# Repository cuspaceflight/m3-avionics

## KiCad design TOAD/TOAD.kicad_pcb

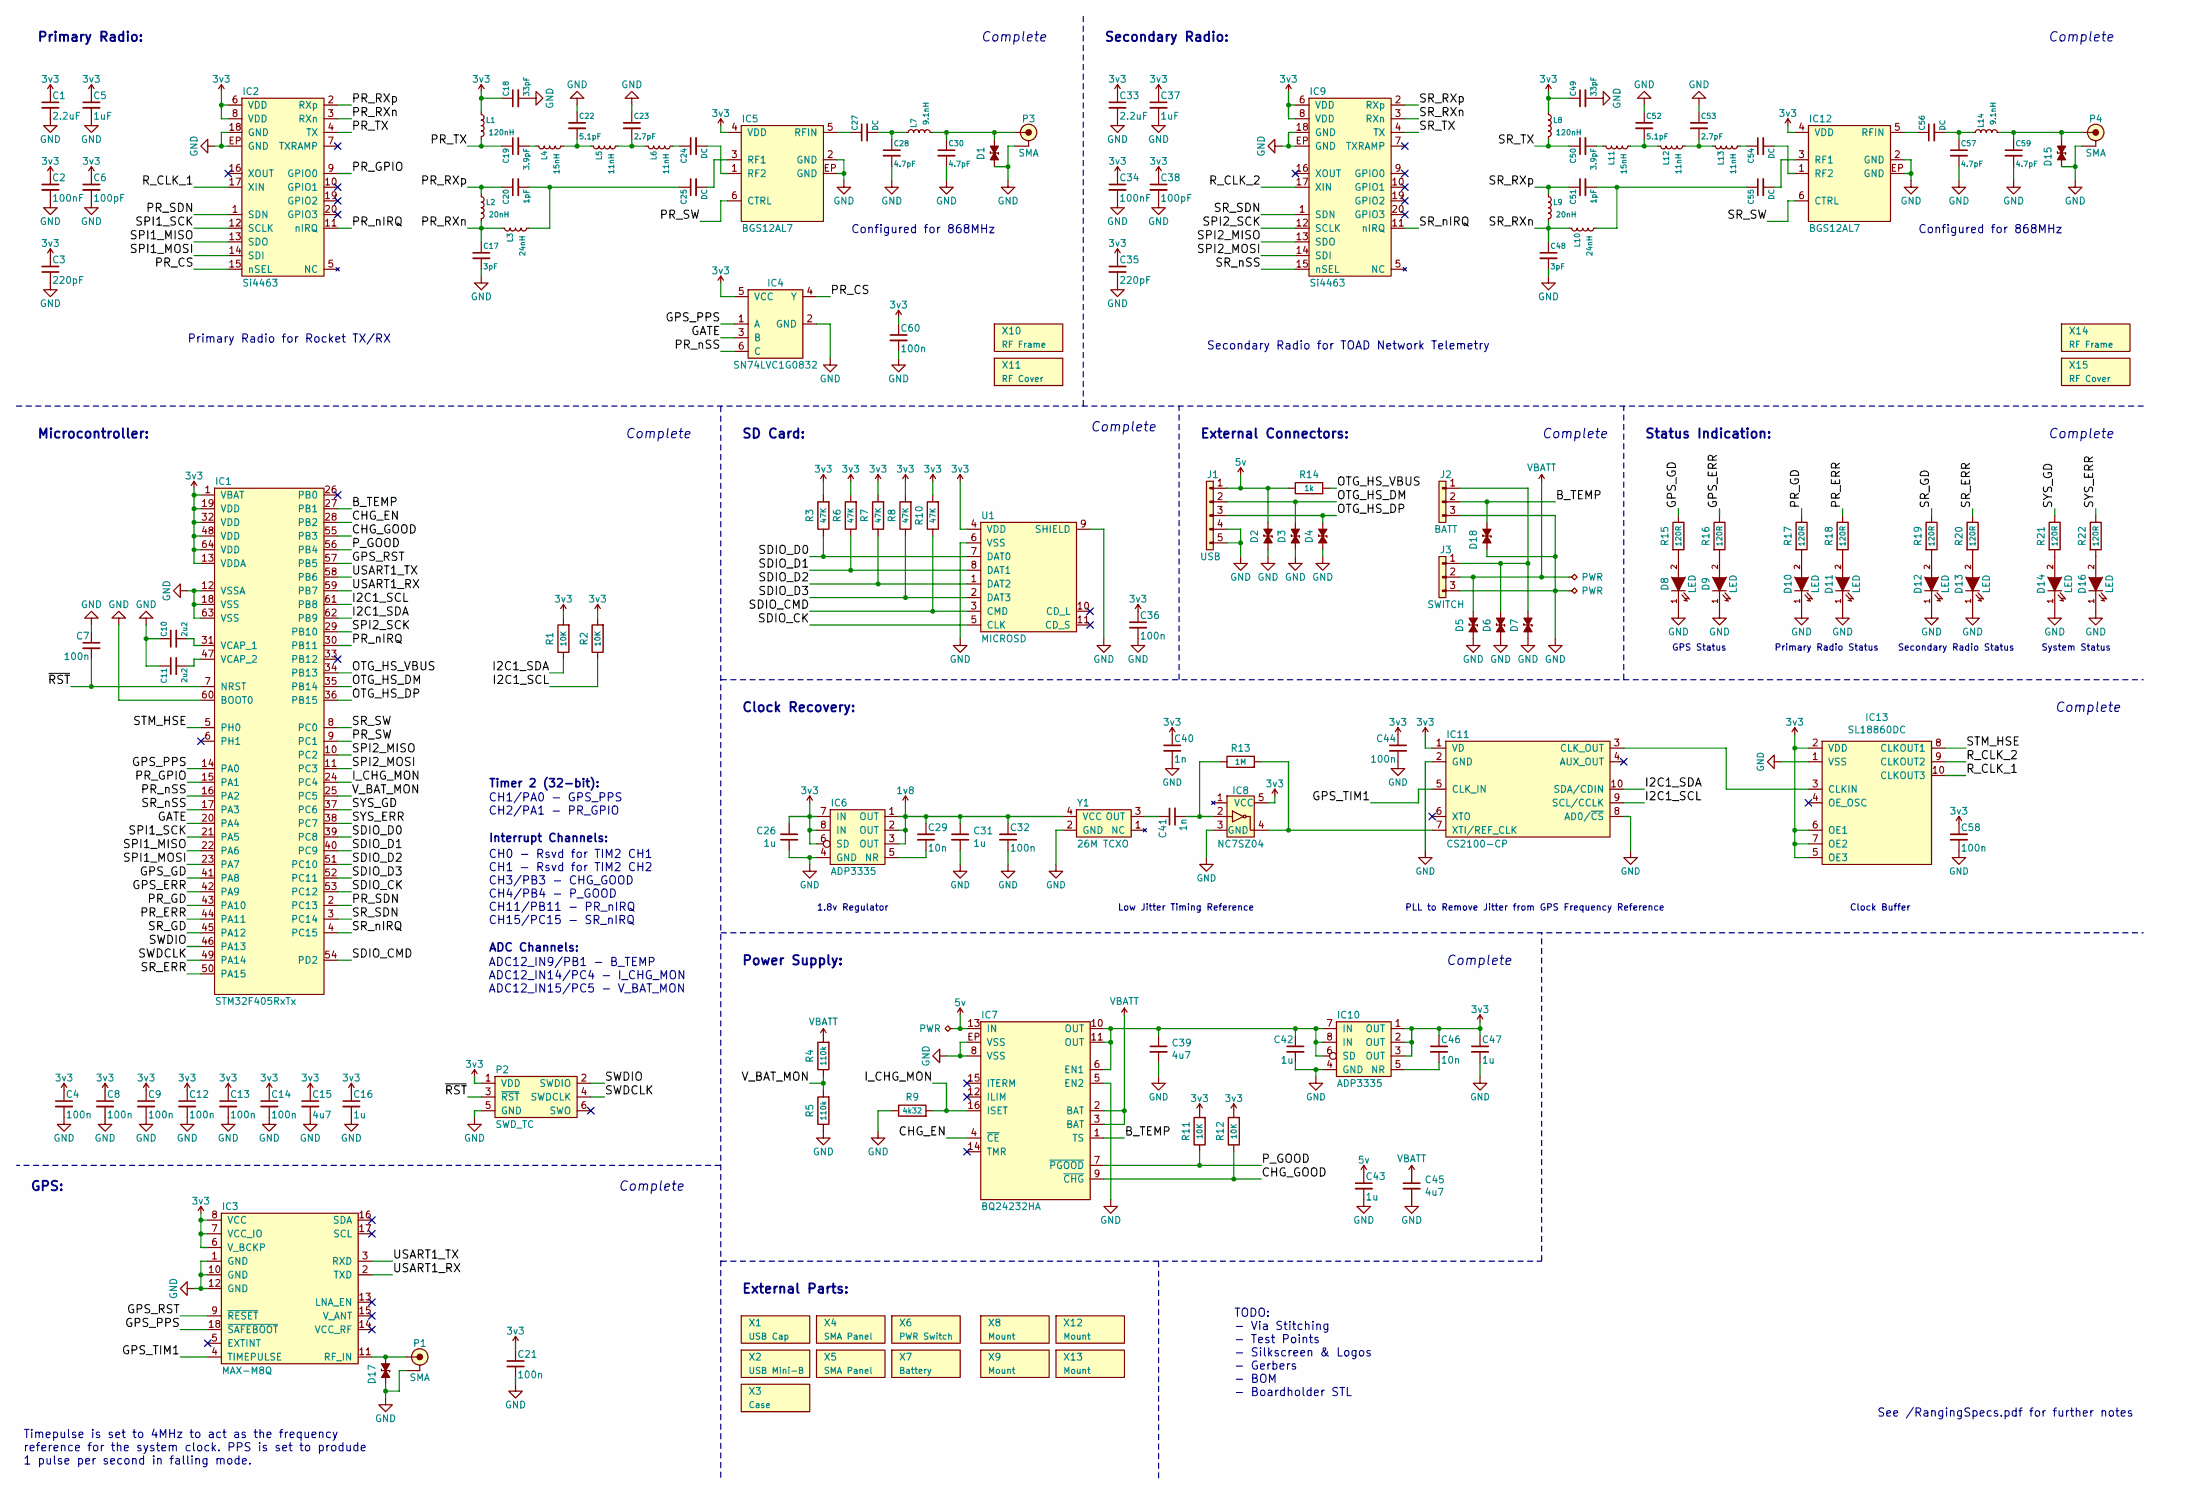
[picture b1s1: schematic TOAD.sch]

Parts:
C1, C33: 2.2uF; 0603-L; Farnell 2346896
C2, C34: 100nF; 0402; Farnell 1828860
C3, C35: 220pF; 0402; Farnell 2496800
C4, C7, C8, C9, C12, C13, C14, C60: 100n; 0402; Farnell 9402047
C5, C37: 1uF; 0603-L; Farnell 2112849
C6, C38: 100pF; 0402; Farnell 2496792
C10, C11: 2u2; 0603-L; Farnell 1797012
C15: 4u7; 0603; Farnell 2496930
C16, C26, C31, C42, C43, C47: 1u; 0603-L; Farnell 1865556
C17, C48: 3pF; 0402; Farnell 2524984
C18, C49: 33pF; 0402; Farnell 2434643
C19, C50: 3.9pF; 0402; Farnell 2672775
C20, C51: 1pF; 0402; Farnell 2133992
C21, C32, C36, C44, C58: 100n; 0603-L; Farnell 2496834
C22, C52: 5.1pF; 0402; Farnell 2688498
C23, C53: 2.7pF; 0402; Farnell 2672771
C24, C25, C27, C54, C55, C56: DC; 0402
C28, C30, C57, C59: 4.7pF; 0402; Farnell 2332509
C29, C46: 10n; 0603-L; Farnell 2496825
C39, C45: 4u7; 0603-L; Farnell 2496930
C40, C41: 1n; 0603-L; Farnell 2496882
D1, D2, D3, D4, D5, D6, D7, D15, D17, D18: ESD_DIODE; 0402-L; Farnell 2368169
D8, D10, D12, D14: LED; 0603-LED; Farnell 2290328
D9, D11, D13, D16: LED; 0603-LED; Farnell 2290329
IC1: STM32F405RxTx; LQFP-64; Farnell 2064363
IC2, IC9: Si4463; QFN-20-EP-SI; Farnell 2462637
IC3: MAX-M8Q
IC4: SN74LVC1G0832; SC-70-6; Farnell 2406965
IC5, IC12: BGS12AL7; TSLP7-4; Farnell 2480594
IC6: ADP3335; MSOP-8; Farnell 2376932
IC7: BQ24232HA; QFN-16-EP-TI; Farnell 2576286
IC8: NC7SZ04; SOT-23-5; Farnell 1417667
IC10: ADP3335; MSOP-8; Farnell 2067775
IC11: CS2100-CP; MSOP-10; Mouser 777-CS2100CP-CZZ
IC13: SL18860DC; DFN-10-SL18860DC; Mouser 634-SL18860DC
J1: USB; SIL-254P-05
J2: BATT; S03B-PASK-2; Farnell 1830748
J3: SWITCH; S03B-PASK-2; Farnell 1830748
L1, L8: 120nH; 0402; Farnell 2285871
L2, L9: 20nH; 0402; Farnell 1748728
L3, L10: 24nH; 0402; Farnell 2470344
L4, L11: 15nH; 0402; Farnell 1762621
L5, L6, L12, L13: 11nH; 0402; Farnell 2116067
L7, L14: 9.1nH; 0402; Farnell 1762616
P1: SMA; SMA-EDGE
P2: SWD_TC; TC2030-NL
P3, P4: SMA; SMA-EDGE; Farnell 1608592
R1, R2, R11, R12: 10K; 0603-L; Farnell 9238603
R3, R6, R7, R8, R10: 47K; 0603-L; Farnell 9238689
R4, R5: 110k; 0603-L; Farnell 2502402
R9: 4k32; 0603-L; Farnell 2670808
R13: 1M; 0603-L; Farnell 1469746
R14: 1k; 0603-L; Farnell 2309108
R15, R16, R17, R18, R19, R20, R21, R22: 120R; 0603-L; Farnell 9238379
U1: MICROSD; MICROSD_MOLEX_503398-1892; Farnell 2358234
X1: USB Cap
X2: USB Mini-B
X3: Case
X4, X5: SMA Panel; Farnell 2096227
X6: PWR Switch
X7: Battery; Farnell 2401856
X8, X9, X12, X13: Mount; M3_MOUNT
X10, X14: RF Frame; BMI-S-201-F; Farnell 2497715
X11, X15: RF Cover; Farnell 2497714
Y1: 26M TCXO; XTAL-25x20; Farnell 2405785

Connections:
1v8: C29.1, C31.1, C32.1, IC6.1 (OUT), IC6.2 (OUT), IC6.3 (OUT), Y1.4 (VCC)
3v3: C1.1, C2.1, C3.1, C4.1, C5.1, C6.1, C8.1, C9.1, C12.1, C13.1, C14.1, C15.1, C16.1, C18.1, C21.1, C26.1, C33.1, C34.1, C35.1, C36.1, C37.1, C38.1, C40.1, C44.1, C46.1, C47.1, C49.1, C58.1, C60.1, IC1.1 (VBAT), IC1.13 (VDDA), IC1.19 (VDD), IC1.32 (VDD), IC1.48 (VDD), IC1.64 (VDD), IC2.6 (VDD), IC2.8 (VDD), IC3.6 (V_BCKP), IC3.7 (VCC_IO), IC3.8 (VCC), IC4.5 (VCC), IC5.4 (VDD), IC6.6 (SD), IC6.7 (IN), IC6.8 (IN), IC8.5 (VCC), IC9.6 (VDD), IC9.8 (VDD), IC10.1 (OUT), IC10.2 (OUT), IC10.3 (OUT), IC11.1 (VD), IC12.4 (VDD), IC13.2 (VDD), IC13.5 (OE3), IC13.6 (OE1), IC13.7 (OE2), L1.1, L8.1, P2.1 (VDD), R1.2, R2.2, R3.2, R6.2, R7.2, R8.2, R10.2, R11.2, R12.2, U1.4 (VDD)
5v: C43.1, D2.1, IC7.13 (IN), J1.1, R14.1
/B_TEMP: D18.1, IC1.27 (PB1), IC7.1 (TS), J2.2
/CHG_EN: IC1.28 (PB2), IC7.4 (~CE)
/CHG_GOOD: IC1.55 (PB3), IC7.9 (~CHG), R12.1
/GATE: IC1.20 (PA4), IC4.3 (B)
/GPS_ERR: IC1.42 (PA9), R16.1
/GPS_GD: IC1.41 (PA8), R15.1
/GPS_PPS: IC1.14 (PA0), IC3.18 (~SAFEBOOT), IC4.1 (A)
/GPS_RST: IC1.57 (PB5), IC3.9 (~RESET)
/GPS_TIM1: IC3.4 (TIMEPULSE), IC11.5 (CLK_IN)
/I2C1_SCL: IC1.61 (PB8), IC11.9 (SCL/CCLK), R2.1
/I2C1_SDA: IC1.62 (PB9), IC11.10 (SDA/CDIN), R1.1
/I_CHG_MON: IC1.24 (PC4), IC7.16 (ISET), R9.2
/OTG_HS_DM: D3.1, IC1.35 (PB14), J1.2
/OTG_HS_DP: D4.1, IC1.36 (PB15), J1.3
/OTG_HS_VBUS: IC1.34 (PB13), R14.2
/PR_CS: IC2.15 (nSEL), IC4.4 (Y)
/PR_ERR: IC1.44 (PA11), R18.1
/PR_GD: IC1.43 (PA10), R17.1
/PR_GPIO: IC1.15 (PA1), IC2.9 (GPIO0)
/PR_RXn: C17.1, IC2.3 (RXn), L2.2, L3.1
/PR_RXp: C20.1, IC2.2 (RXp), L2.1
/PR_SDN: IC1.2 (PC13), IC2.1 (SDN)
/PR_SW: IC1.9 (PC1), IC5.6 (CTRL)
/PR_TX: C19.1, IC2.4 (TX), L1.2
/PR_nIRQ: IC1.30 (PB11), IC2.11 (nIRQ)
/PR_nSS: IC1.16 (PA2), IC4.6 (C)
/P_GOOD: IC1.56 (PB4), IC7.7 (~PGOOD), R11.1
/R_CLK_1: IC2.17 (XIN), IC13.10 (CLKOUT3)
/R_CLK_2: IC9.17 (XIN), IC13.9 (CLKOUT2)
/SDIO_CK: IC1.53 (PC12), U1.5 (CLK)
/SDIO_CMD: IC1.54 (PD2), R10.1, U1.3 (CMD)
/SDIO_D0: IC1.39 (PC8), R3.1, U1.7 (DAT0)
/SDIO_D1: IC1.40 (PC9), R6.1, U1.8 (DAT1)
/SDIO_D2: IC1.51 (PC10), R7.1, U1.1 (DAT2)
/SDIO_D3: IC1.52 (PC11), R8.1, U1.2 (DAT3)
/SPI1_MISO: IC1.22 (PA6), IC2.13 (SDO)
/SPI1_MOSI: IC1.23 (PA7), IC2.14 (SDI)
/SPI1_SCK: IC1.21 (PA5), IC2.12 (SCLK)
/SPI2_MISO: IC1.10 (PC2), IC9.13 (SDO)
/SPI2_MOSI: IC1.11 (PC3), IC9.14 (SDI)
/SPI2_SCK: IC1.29 (PB10), IC9.12 (SCLK)
/SR_ERR: IC1.50 (PA15), R20.1
/SR_GD: IC1.45 (PA12), R19.1
/SR_RXn: C48.1, IC9.3 (RXn), L9.2, L10.1
/SR_RXp: C51.1, IC9.2 (RXp), L9.1
/SR_SDN: IC1.3 (PC14), IC9.1 (SDN)
/SR_SW: IC1.8 (PC0), IC12.6 (CTRL)
/SR_TX: C50.1, IC9.4 (TX), L8.2
/SR_nIRQ: IC1.4 (PC15), IC9.11 (nIRQ)
/SR_nSS: IC1.17 (PA3), IC9.15 (nSEL)
/STM_HSE: IC1.5 (PH0), IC13.8 (CLKOUT1)
/SWDCLK: IC1.49 (PA14), P2.4 (SWDCLK)
/SWDIO: IC1.46 (PA13), P2.2 (SWDIO)
/SYS_ERR: IC1.38 (PC7), R22.1
/SYS_GD: IC1.37 (PC6), R21.1
/USART1_RX: IC1.59 (PB7), IC3.2 (TXD)
/USART1_TX: IC1.58 (PB6), IC3.3 (RXD)
/V_BAT_MON: IC1.25 (PC5), R4.1, R5.2
/~RST: C7.2, IC1.7 (NRST), P2.3 (~RST)
GND: C1.2, C2.2, C3.2, C4.2, C5.2, C6.2, C7.1, C8.2, C9.2, C10.1, C11.1, C12.2, C13.2, C14.2, C15.2, C16.2, C17.2, C18.2, C21.2, C22.1, C23.1, C26.2, C28.2, C30.2, C31.2, C32.2, C33.2, C34.2, C35.2, C36.2, C37.2, C38.2, C39.2, C40.2, C42.2, C43.2, C44.2, C45.2, C47.2, C48.2, C49.2, C52.1, C53.1, C57.2, C58.2, C59.2, C60.2, D1.2, D2.2, D3.2, D4.2, D5.2, D6.2, D7.2, D8.1 (K), D9.1 (K), D10.1 (K), D11.1 (K), D12.1 (K), D13.1 (K), D14.1 (K), D15.2, D16.1 (K), D17.2, D18.2, IC1.12 (VSSA), IC1.18 (VSS), IC1.60 (BOOT0), IC1.63 (VSS), IC2.18 (GND), IC2.EP (GND), IC3.1 (GND), IC3.10 (GND), IC3.12 (GND), IC4.2 (GND), IC5.2 (GND), IC5.EP (GND), IC6.4 (GND), IC7.5 (EN2), IC7.8 (VSS), IC7.EP (VSS), IC8.3 (GND), IC9.18 (GND), IC9.EP (GND), IC10.4 (GND), IC11.2 (GND), IC11.8 (AD0/~CS), IC12.2 (GND), IC12.EP (GND), IC13.1 (VSS), J1.4, J1.5, J2.3, J3.3, P1.2 (GND), P2.5 (GND), P3.2 (GND), P4.2 (GND), R5.1, R9.1, U1.6 (VSS), U1.9 (SHIELD), Y1.2 (GND)
unnamed: C10.2, IC1.31 (VCAP_1)
unnamed: C11.2, IC1.47 (VCAP_2)
unnamed: C19.2, L4.1
unnamed: C20.2, C25.1, L3.2
unnamed: C22.2, L4.2, L5.1
unnamed: C23.2, L5.2, L6.1
unnamed: C24.1, L6.2
unnamed: C24.2, IC5.1 (RF2)
unnamed: C25.2, IC5.3 (RF1)
unnamed: C27.1, IC5.5 (RFIN)
unnamed: C27.2, C28.1, L7.1
unnamed: C29.2, IC6.5 (NR)
unnamed: C30.1, D1.1, L7.2, P3.1 (RF)
unnamed: C39.1, C42.1, IC7.6 (EN1), IC7.10 (OUT), IC7.11 (OUT), IC10.6 (SD), IC10.7 (IN), IC10.8 (IN)
unnamed: C41.1, Y1.3 (OUT)
unnamed: C41.2, IC8.2, R13.1
unnamed: C46.2, IC10.5 (NR)
unnamed: C50.2, L11.1
unnamed: C51.2, C55.1, L10.2
unnamed: C52.2, L11.2, L12.1
unnamed: C53.2, L12.2, L13.1
unnamed: C54.1, L13.2
unnamed: C54.2, IC12.1 (RF2)
unnamed: C55.2, IC12.3 (RF1)
unnamed: C56.1, IC12.5 (RFIN)
unnamed: C56.2, C57.1, L14.1
unnamed: C59.1, D15.1, L14.2, P4.1 (RF)
unnamed: D6.1, D7.1, J2.1, J3.1
unnamed: D8.2 (A), R15.2
unnamed: D9.2 (A), R16.2
unnamed: D10.2 (A), R17.2
unnamed: D11.2 (A), R18.2
unnamed: D12.2 (A), R19.2
unnamed: D13.2 (A), R20.2
unnamed: D14.2 (A), R21.2
unnamed: D16.2 (A), R22.2
unnamed: D17.1, IC3.11 (RF_IN), P1.1 (RF)
unnamed: IC11.3 (CLK_OUT), IC13.3 (CLKIN)
unnamed: IC8.4, IC11.7 (XTI/REF_CLK), R13.2
VBATT: C45.1, D5.1, IC7.2 (BAT), IC7.3 (BAT), J3.2, R4.2

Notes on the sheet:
Configured for 868MHz
Primary Radio:
Microcontroller:
Complete
Secondary Radio:
GPS:
SD Card:
External Connectors:
Timepulse is set to 4MHz to act as the frequency reference for the system clock. PPS is set to produde 1 pulse per second in falling mode.
Clock Recovery:
Power Supply:
1.8v Regulator
Low Jitter Timing Reference
PLL to Remove Jitter from GPS Frequency Reference
Status Indication:
GPS Status
Primary Radio Status
Secondary Radio Status
System Status
Clock Buffer
Primary Radio for Rocket TX/RX
Secondary Radio for TOAD Network Telemetry
TODO: - Via Stitching - Test Points - Silkscreen & Logos - Gerbers - BOM - Boardholder STL
CH1/PA0 - GPS_PPS CH2/PA1 - PR_GPIO
Timer 2 (32-bit):
CH0 - Rsvd for TIM2 CH1 CH1 - Rsvd for TIM2 CH2 CH3/PB3 - CHG_GOOD CH4/PB4 - P_GOOD CH11/PB11 - PR_nIRQ CH15/PC15 - SR_nIRQ
Interrupt Channels:
ADC Channels:
ADC12_IN9/PB1 - B_TEMP ADC12_IN14/PC4 - I_CHG_MON ADC12_IN15/PC5 - V_BAT_MON
External Parts:
See /RangingSpecs.pdf for further notes

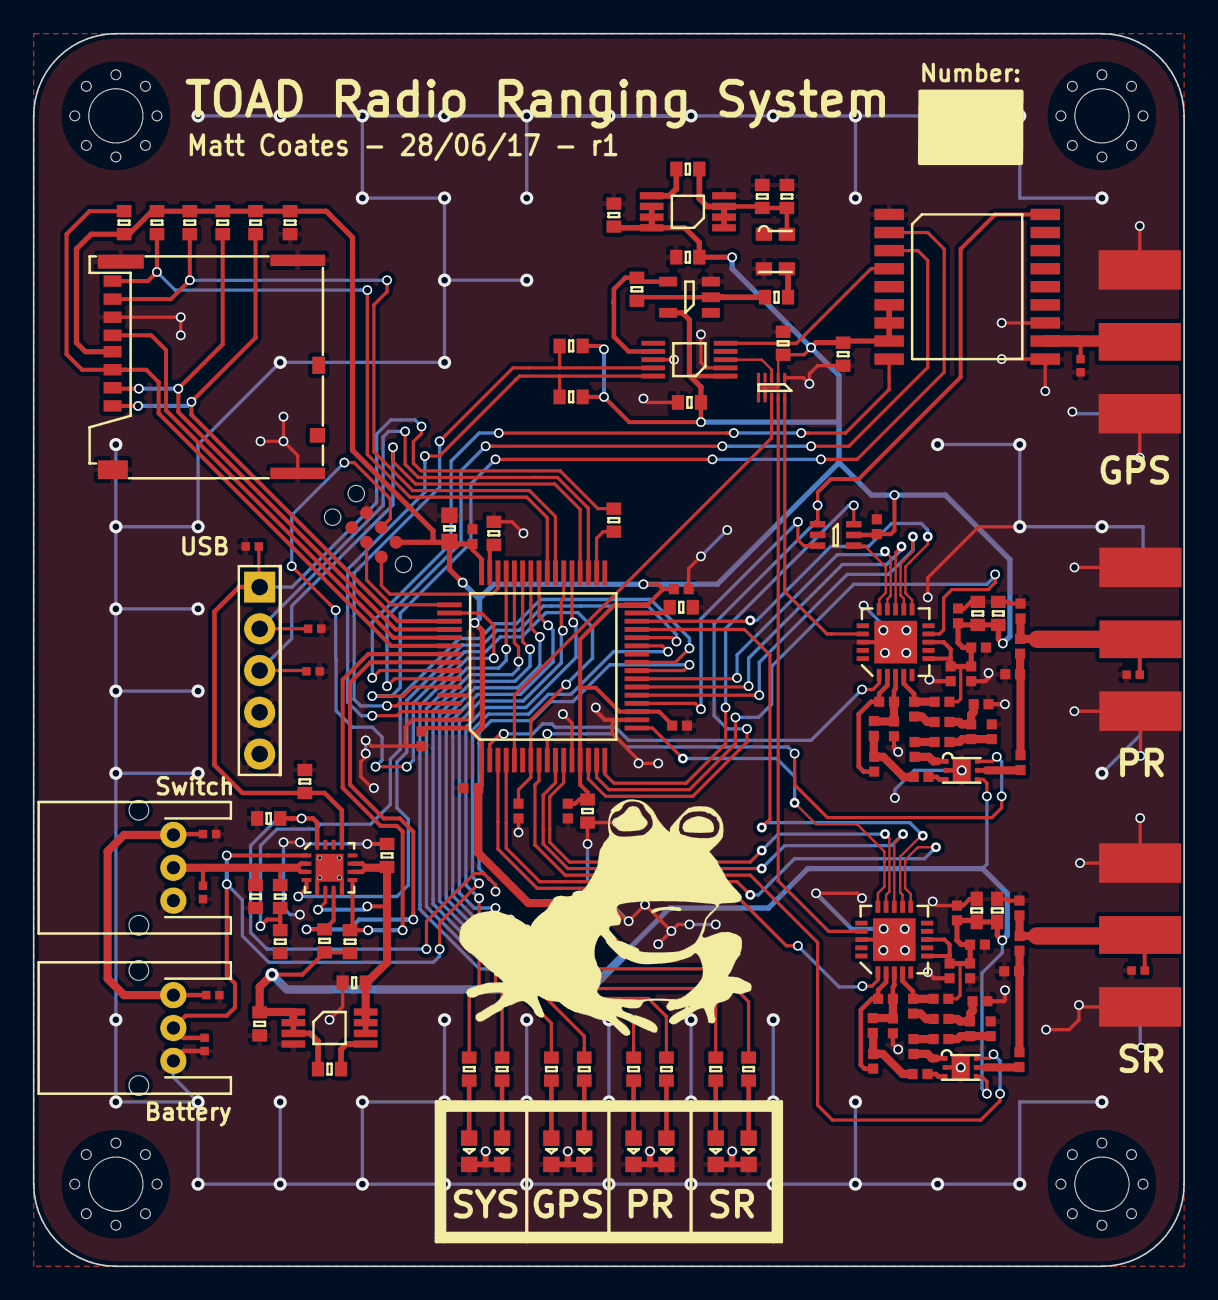
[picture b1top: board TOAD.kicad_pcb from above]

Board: 2 copper layers, 70.0 x 75.0 mm, 142 parts (0 on the bottom side), 103 nets.

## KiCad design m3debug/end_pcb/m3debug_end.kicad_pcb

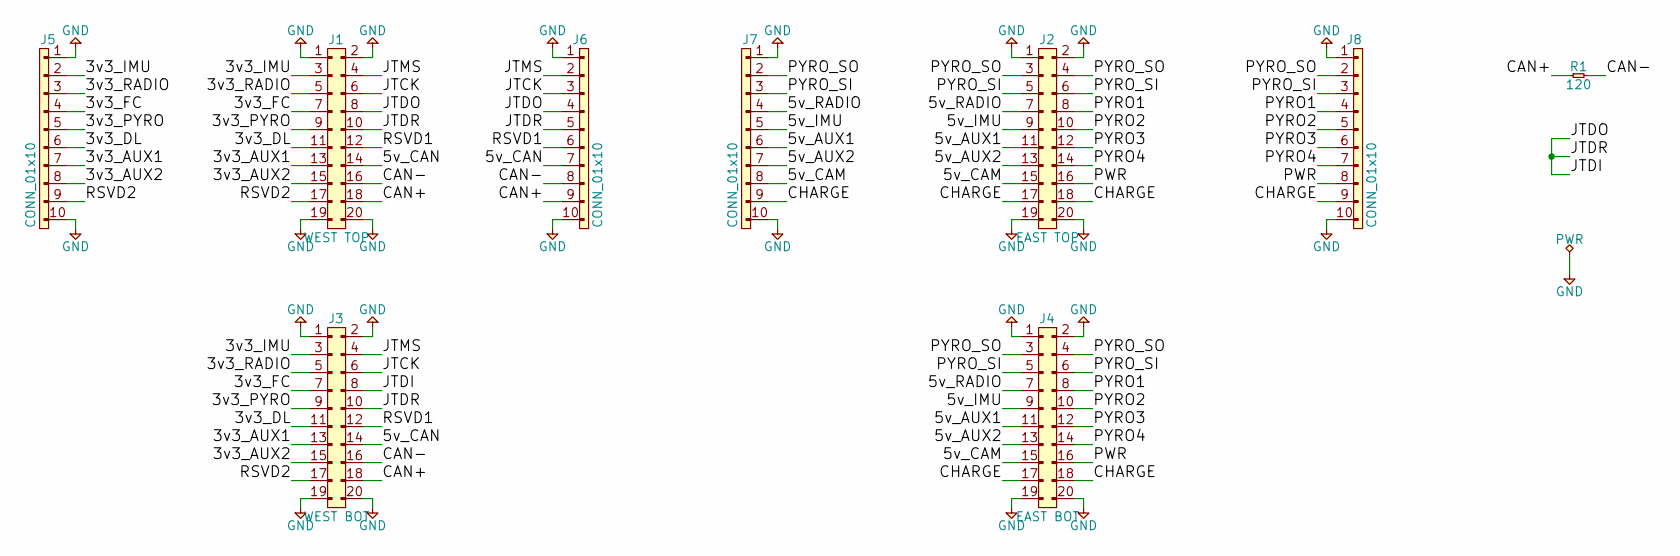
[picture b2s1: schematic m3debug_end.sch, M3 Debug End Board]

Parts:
J1: WEST TOP; TFML-110-02-L-D
J2: EAST TOP; TFML-110-02-L-D
J3: WEST BOT; SFML-110-02-L-D-LC
J4: EAST BOT; SFML-110-02-L-D-LC
J5, J6, J7, J8: CONN_01x10; SIL-254P-10
R1: 120; 0402

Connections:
/3v3_AUX1: J1.13, J3.13, J5.7
/3v3_AUX2: J1.15, J3.15, J5.8
/3v3_DL: J1.11, J3.11, J5.6
/3v3_FC: J1.7, J3.7, J5.4
/3v3_IMU: J1.3, J3.3, J5.2
/3v3_PYRO: J1.9, J3.9, J5.5
/3v3_RADIO: J1.5, J3.5, J5.3
/5v_AUX1: J2.11, J4.11, J7.6
/5v_AUX2: J2.13, J4.13, J7.7
/5v_CAM: J2.15, J4.15, J7.8
/5v_CAN: J1.14, J3.14, J6.7
/5v_IMU: J2.9, J4.9, J7.5
/5v_RADIO: J2.7, J4.7, J7.4
/CAN+: J1.18, J3.18, J6.9, R1.1
/CAN-: J1.16, J3.16, J6.8, R1.2
/CHARGE: J2.17, J2.18, J4.17, J4.18, J7.9, J8.9
/JTCK: J1.6, J3.6, J6.3
/JTDI: J1.8, J1.10, J3.8, J3.10, J6.4, J6.5
/JTMS: J1.4, J3.4, J6.2
/PWR: J2.16, J4.16, J8.8
/PYRO1: J2.8, J4.8, J8.4
/PYRO2: J2.10, J4.10, J8.5
/PYRO3: J2.12, J4.12, J8.6
/PYRO4: J2.14, J4.14, J8.7
/PYRO_SI: J2.5, J2.6, J4.5, J4.6, J7.3, J8.3
/PYRO_SO: J2.3, J2.4, J4.3, J4.4, J7.2, J8.2
/RSVD1: J1.12, J3.12, J6.6
/RSVD2: J1.17, J3.17, J5.9
GND: J1.1, J1.2, J1.19, J1.20, J2.1, J2.2, J2.19, J2.20, J3.1, J3.2, J3.19, J3.20, J4.1, J4.2, J4.19, J4.20, J5.1, J5.10, J6.1, J6.10, J7.1, J7.10, J8.1, J8.10

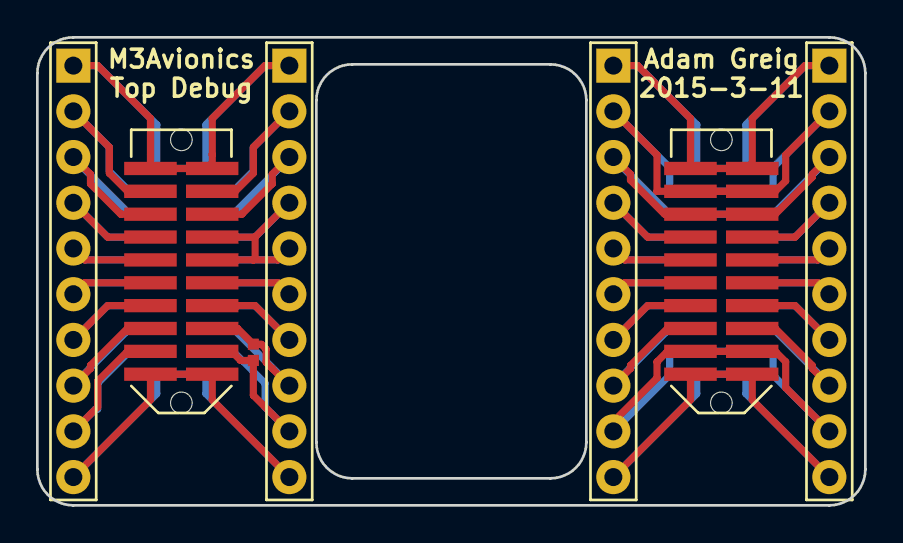
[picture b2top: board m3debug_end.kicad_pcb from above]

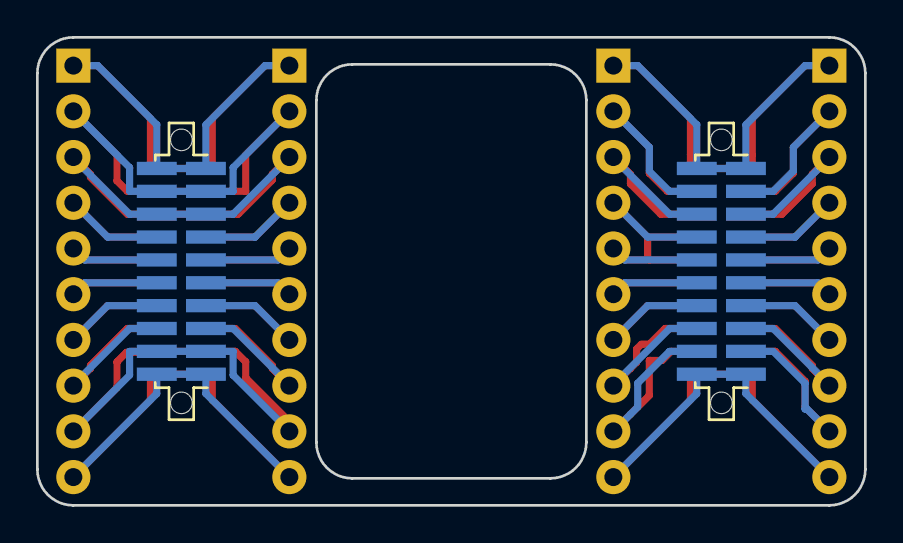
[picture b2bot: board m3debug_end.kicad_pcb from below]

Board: 2 copper layers, 46.0 x 26.0 mm, 9 parts (2 on the bottom side), 29 nets.

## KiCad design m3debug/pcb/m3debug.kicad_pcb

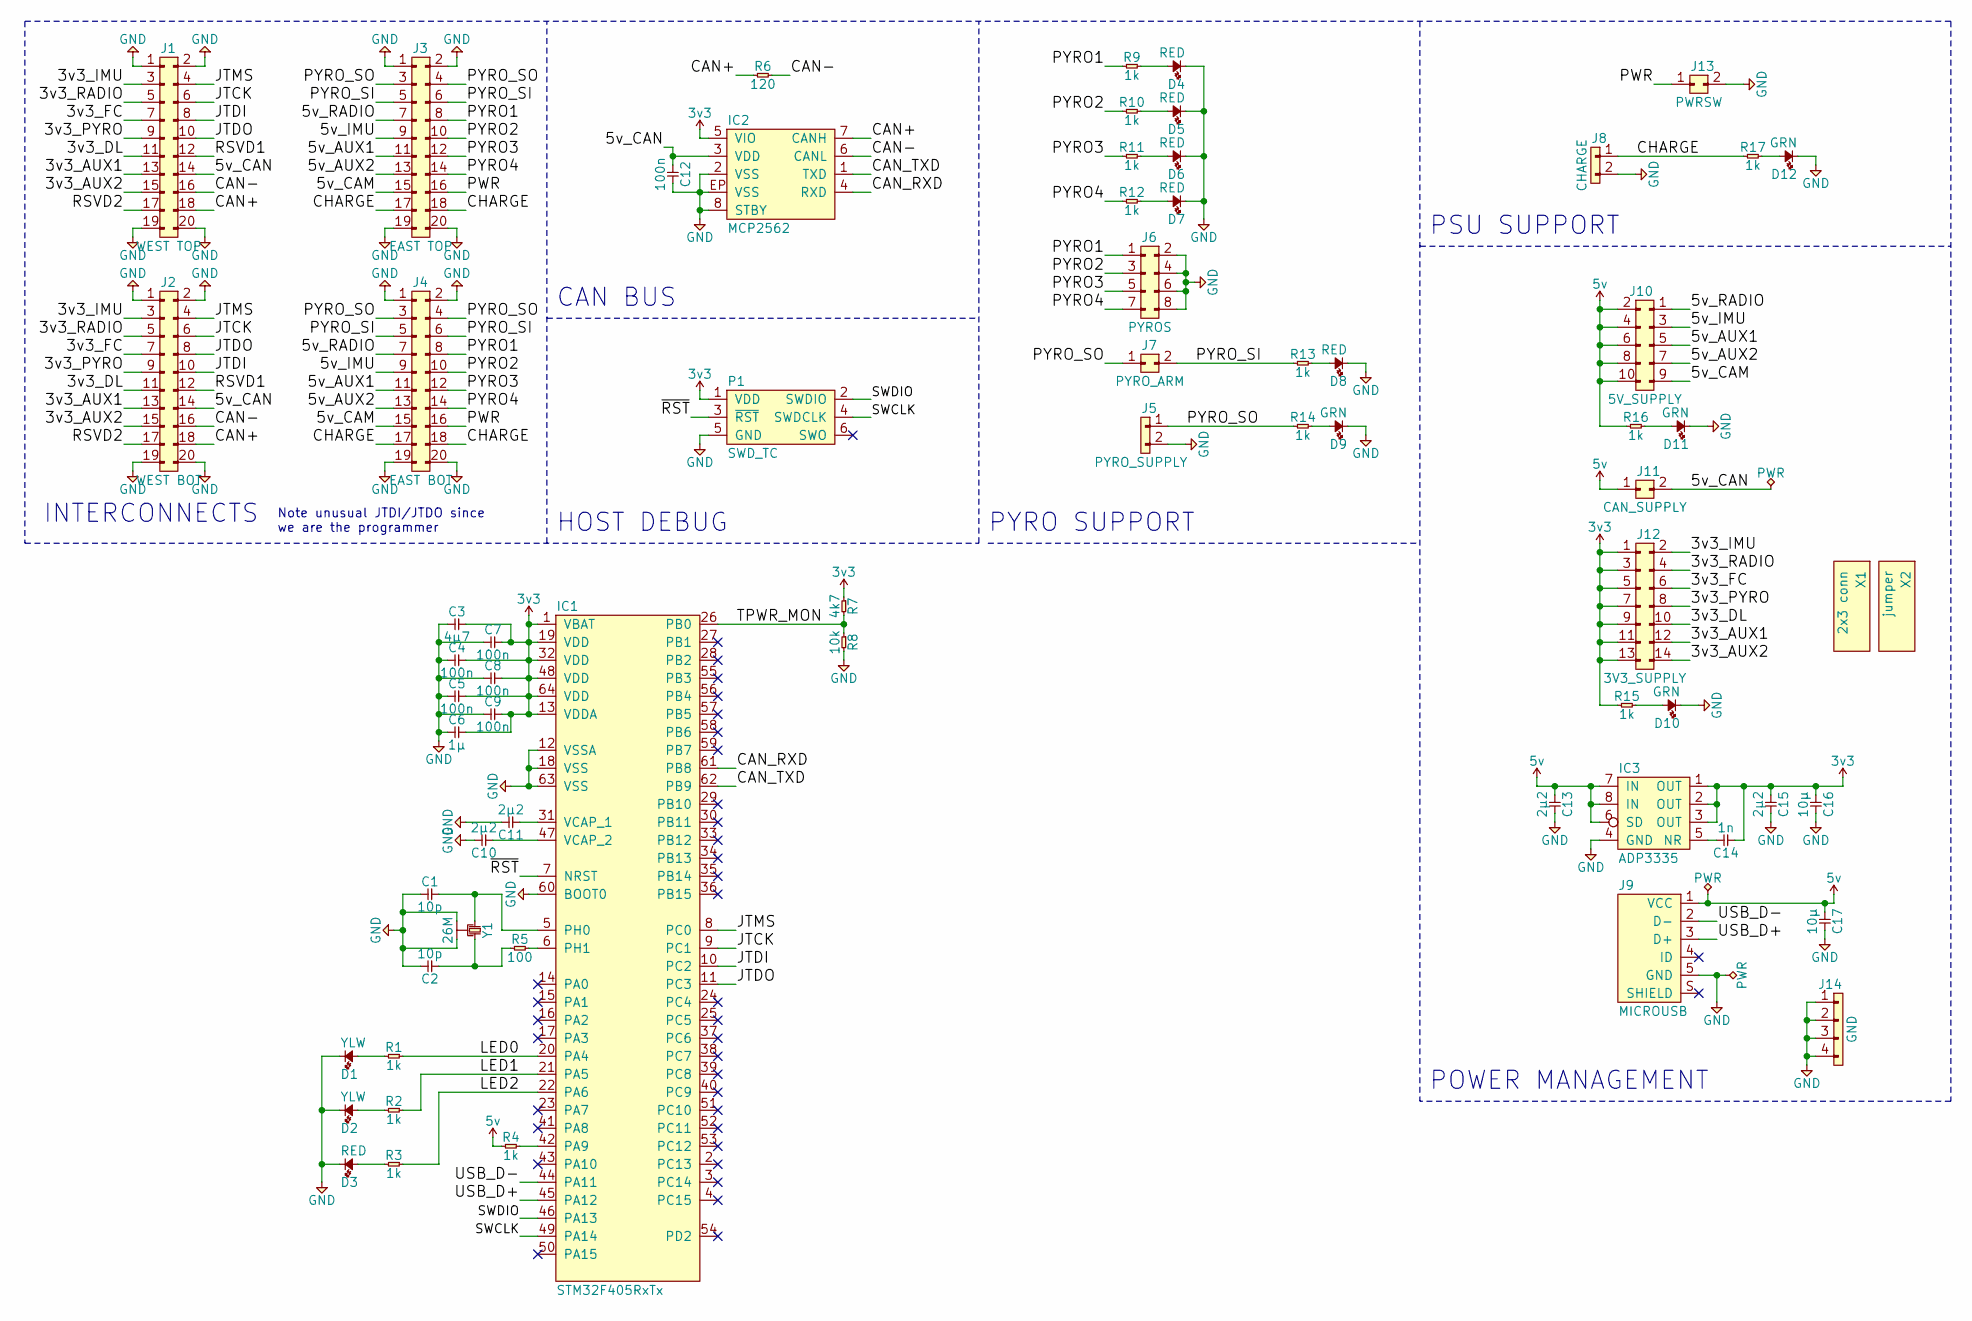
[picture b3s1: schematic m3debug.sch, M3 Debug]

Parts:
C1, C2: 10p; 0402; Farnell 2496790
C3: 4µ7; 0402; Farnell 2426952
C4, C5, C7, C8, C9, C12: 100n; 0402; Farnell 2496771
C6: 1µ; 0402; Farnell 2496814
C10, C11: 2µ2; 0402; Farnell 2362088
C13, C15: 2µ2; 0603; Farnell 2496923
C14: 1n; 0402; Farnell 2496767
C16, C17: 10µ; 0603; Farnell 2456110
D1, D2: YLW; 0603-LED; Farnell 2290330
D3, D4, D5, D6, D7, D8: RED; 0603-LED; Farnell 2290329
D9, D10, D11, D12: GRN; 0603-LED; Farnell 2290328
IC1: STM32F405RxTx; LQFP-64; Farnell 2064363
IC2: MCP2562; DFN-8-EP-MICROCHIP; Farnell 2448755
IC3: ADP3335; MSOP-8; Farnell 2067775
J1: WEST TOP; TFML-110-02-L-D
J2: WEST BOT; SFML-110-02-L-D-LC
J3: EAST TOP; TFML-110-02-L-D
J4: EAST BOT; SFML-110-02-L-D-LC
J5: PYRO_SUPPLY; S02B-PASK-2; Farnell 1830747
J6: PYROS; DIL-254P-08; Farnell 1022232
J7: PYRO_ARM; SIL-254P-02; Farnell 1022245
J8: CHARGE; S02B-PASK-2; Farnell 1830747
J9: MICROUSB; MICROUSB_MOLEX_47589-0001; Farnell 1568023
J10: 5V_SUPPLY; DIL-254P-10; Farnell 1022235
J11: CAN_SUPPLY; SIL-254P-02; Farnell 1022245
J12: 3V3_SUPPLY; DIL-254P-14; Farnell 1022232
J13: PWRSW; SIL-254P-02; Farnell 1022245
J14: GND; SIL-254P-04; Farnell 1022250
P1: SWD_TC; TC2030-NL
R1, R2, R3, R4, R9, R10, R11, R12, R13, R14, R15, R16, R17: 1k; 0402; Farnell 9232761
R5: 100; 0402; Farnell 9239111
R6: 120; 0402; Farnell 2072575
R7: 4k7; 0402; Farnell 1358060
R8: 10k; 0402; Farnell 1358069
X1: 2x3 conn; Farnell 1022230
X2: jumper; Farnell 2396303
Y1: 26M; XTAL-20x16; Farnell 2506952

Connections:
3v3: C3.2, C4.2, C5.2, C6.2, C7.2, C8.2, C9.2, C14.1, C15.1, C16.1, IC1.1 (VBAT), IC1.13 (VDDA), IC1.19 (VDD), IC1.32 (VDD), IC1.48 (VDD), IC1.64 (VDD), IC2.5 (VIO), IC3.1 (OUT), IC3.2 (OUT), IC3.3 (OUT), J12.1, J12.3, J12.5, J12.7, J12.9, J12.11, J12.13, P1.1 (VDD), R7.1, R15.1
5v: C13.1, C17.1, IC3.6 (SD), IC3.7 (IN), IC3.8 (IN), J9.1 (VCC), J10.2, J10.4, J10.6, J10.8, J10.10, J11.1, R4.1, R16.1
/3v3_AUX1: J1.13, J2.13, J12.12
/3v3_AUX2: J1.15, J2.15, J12.14
/3v3_DL: J1.11, J2.11, J12.10
/3v3_FC: J1.7, J2.7, J12.6
/3v3_IMU: J1.3, J2.3, J12.2
/3v3_PYRO: J1.9, J2.9, J12.8
/3v3_RADIO: J1.5, J2.5, J12.4
/5v_AUX1: J3.11, J4.11, J10.5
/5v_AUX2: J3.13, J4.13, J10.7
/5v_CAM: J3.15, J4.15, J10.9
/5v_CAN: C12.1, IC2.3 (VDD), J1.14, J2.14, J11.2
/5v_IMU: J3.9, J4.9, J10.3
/5v_RADIO: J3.7, J4.7, J10.1
/CAN+: IC2.7 (CANH), J1.18, J2.18, R6.1
/CAN-: IC2.6 (CANL), J1.16, J2.16, R6.2
/CAN_RXD: IC1.61 (PB8), IC2.4 (RXD)
/CAN_TXD: IC1.62 (PB9), IC2.1 (TXD)
/CHARGE: J3.17, J3.18, J4.17, J4.18, J8.1, R17.1
/JTCK: IC1.9 (PC1), J1.6, J2.6
/JTDI: IC1.10 (PC2), J1.8, J2.10
/JTDO: IC1.11 (PC3), J1.10, J2.8
/JTMS: IC1.8 (PC0), J1.4, J2.4
/LED0: IC1.20 (PA4), R1.1
/LED1: IC1.21 (PA5), R2.1
/LED2: IC1.22 (PA6), R3.1
/PWR: J3.16, J4.16, J13.1
/PYRO1: J3.8, J4.8, J6.1, R9.1
/PYRO2: J3.10, J4.10, J6.3, R10.1
/PYRO3: J3.12, J4.12, J6.5, R11.1
/PYRO4: J3.14, J4.14, J6.7, R12.1
/PYRO_SI: J3.5, J3.6, J4.5, J4.6, J7.2, R13.1
/PYRO_SO: J3.3, J3.4, J4.3, J4.4, J5.1, J7.1, R14.1
/RSVD1: J1.12, J2.12
/RSVD2: J1.17, J2.17
/SWCLK: IC1.49 (PA14), P1.4 (SWDCLK)
/SWDIO: IC1.46 (PA13), P1.2 (SWDIO)
/TPWR_MON: IC1.26 (PB0), R7.2, R8.1
/USB_D+: IC1.45 (PA12), J9.3 (D+)
/USB_D-: IC1.44 (PA11), J9.2 (D-)
/~RST: IC1.7 (NRST), P1.3 (~RST)
GND: C1.1, C2.2, C3.1, C4.1, C5.1, C6.1, C7.1, C8.1, C9.1, C10.2, C11.2, C12.2, C13.2, C15.2, C16.2, C17.2, D1.1, D2.1, D3.1, D4.1, D5.1, D6.1, D7.1, D8.1, D9.1, D10.1, D11.1, D12.1, IC1.12 (VSSA), IC1.18 (VSS), IC1.60 (BOOT0), IC1.63 (VSS), IC2.2 (VSS), IC2.8 (STBY), IC2.EP (VSS), IC3.4 (GND), J1.1, J1.2, J1.19, J1.20, J2.1, J2.2, J2.19, J2.20, J3.1, J3.2, J3.19, J3.20, J4.1, J4.2, J4.19, J4.20, J5.2, J6.2, J6.4, J6.6, J6.8, J8.2, J9.5 (GND), J13.2, J14.1, J14.2, J14.3, J14.4, P1.5 (GND), R8.2, Y1.2, Y1.4
unnamed: C1.2, IC1.5 (PH0), Y1.1
unnamed: C2.1, R5.1, Y1.3
unnamed: C10.1, IC1.47 (VCAP_2)
unnamed: C11.1, IC1.31 (VCAP_1)
unnamed: C14.2, IC3.5 (NR)
unnamed: D1.2, R1.2
unnamed: D2.2, R2.2
unnamed: D3.2, R3.2
unnamed: D4.2, R9.2
unnamed: D5.2, R10.2
unnamed: D6.2, R11.2
unnamed: D7.2, R12.2
unnamed: D8.2, R13.2
unnamed: D9.2, R14.2
unnamed: D10.2, R15.2
unnamed: D11.2, R16.2
unnamed: D12.2, R17.2
unnamed: IC1.6 (PH1), R5.2
unnamed: IC1.42 (PA9), R4.2

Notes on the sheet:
INTERCONNECTS
CAN BUS
HOST DEBUG
Note unusual JTDI/JTDO since we are the programmer
PYRO SUPPORT
PSU SUPPORT
POWER MANAGEMENT

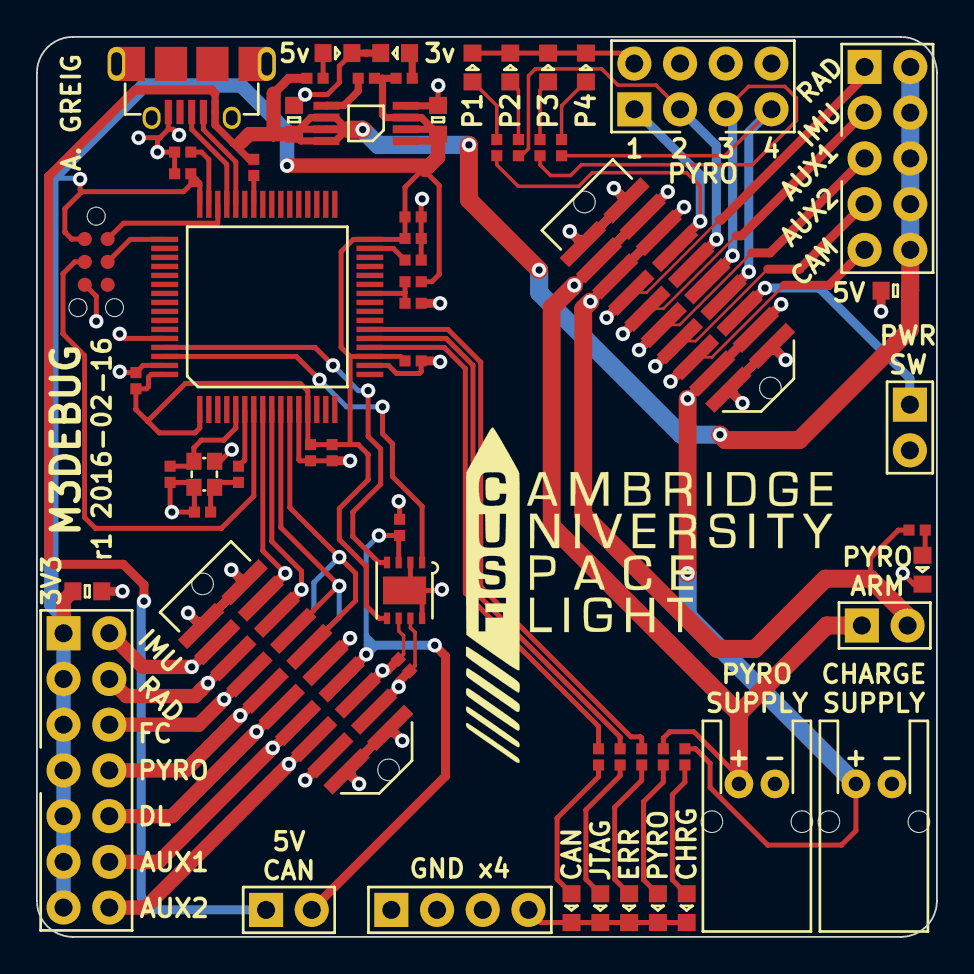
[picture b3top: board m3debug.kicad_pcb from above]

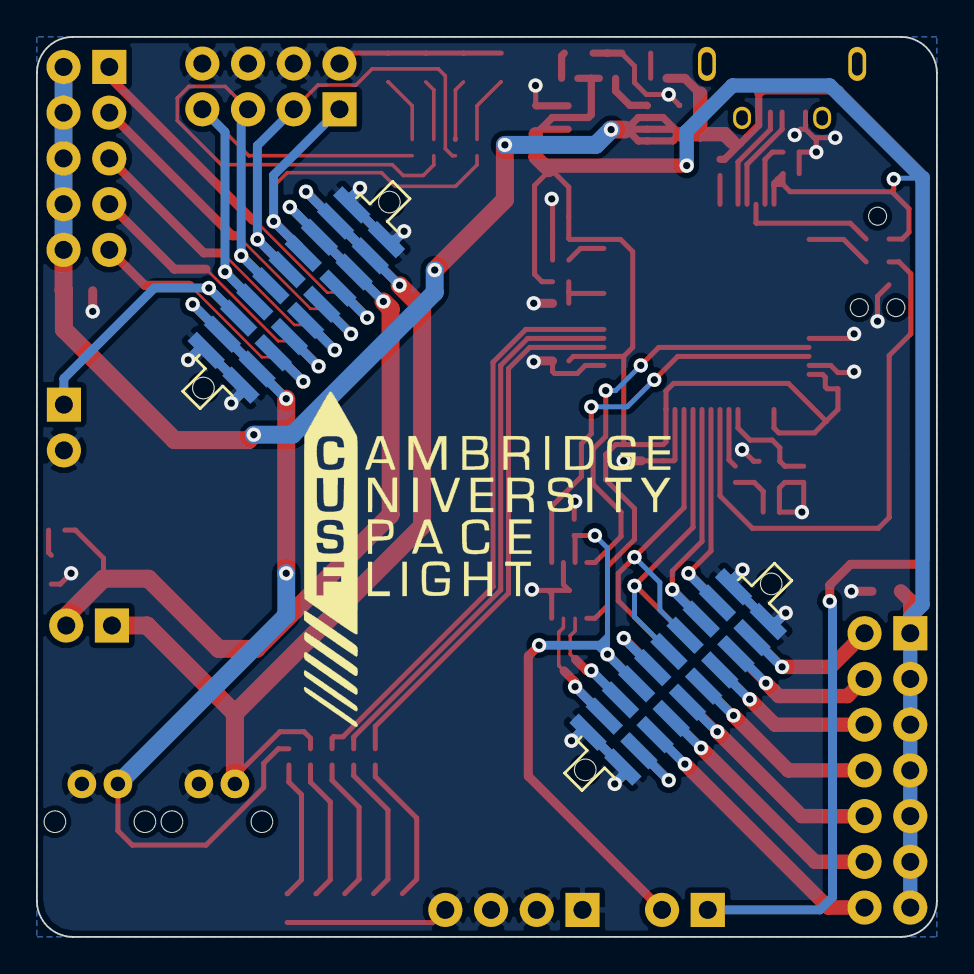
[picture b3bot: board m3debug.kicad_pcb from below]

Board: 2 copper layers, 50.0 x 50.0 mm, 65 parts (2 on the bottom side), 62 nets.

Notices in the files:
m3dl/extpressure/firmware/board.h:
ChibiOS - Copyright (C) 2006..2016 Giovanni Di Sirio
Licensed under the Apache License, Version 2.0 (the "License");
